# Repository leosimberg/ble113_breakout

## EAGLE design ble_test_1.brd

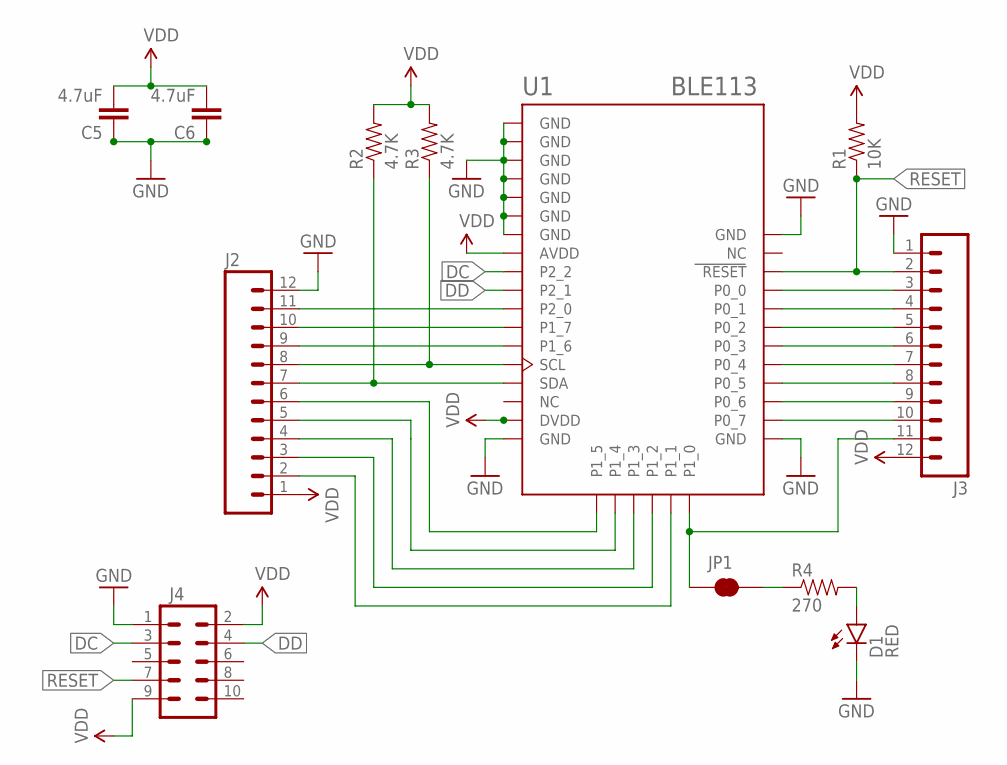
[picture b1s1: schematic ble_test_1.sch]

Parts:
C5, C6: 4.7uF; 0603-CAP
D1: RED; LED-0603
J2, J3: M12PTH; 1X12
J4: M05X2PTH; AVR_ICSP
JP1: JUMPER-PAD-2-NC_BY_TRACE; PAD-JUMPER-2-NC_BY_TRACE_YES_SILK
R1: 10K; 0603-RES
R2, R3: 4.7K; 0603-RES
R4: 270; 0603-RES
U1: BLE113; BLE113-A

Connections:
DC: J4.3, U1.P2_2
DD: J4.4, U1.P2_1
GND: C5.1, C6.1, D1.C, J2.12, J3.1, J4.1, U1.GND, U1.GND@2 (GND), U1.GND@3 (GND), U1.GND@4 (GND), U1.GND@5 (GND), U1.GND@6 (GND), U1.GND@7 (GND), U1.GND@8 (GND), U1.GND@9 (GND), U1.GND@10 (GND)
unnamed: J3.8, U1.P0_5
unnamed: J2.11, U1.P2_0
unnamed: J3.7, U1.P0_4
unnamed: J3.4, U1.P0_1
unnamed: J2.10, U1.P1_7
unnamed: J3.5, U1.P0_2
unnamed: J3.6, U1.P0_3
unnamed: J3.10, U1.P0_7
unnamed: J3.9, U1.P0_6
unnamed: J2.2, U1.P1_1
unnamed: D1.A, R4.2
unnamed: J3.3, U1.P0_0
unnamed: J3.11, JP1.1, U1.P1_0
unnamed: J2.9, U1.P1_6
unnamed: J2.6, U1.P1_5
unnamed: JP1.2, R4.1
unnamed: J2.5, U1.P1_4
unnamed: J2.3, U1.P1_2
unnamed: J2.4, U1.P1_3
RESET: J3.2, J4.7, R1.1, U1.RESET
SCL: J2.7, R2.1, U1.SDA
SDA: J2.8, R3.1, U1.SCL
VDD: C5.2, C6.2, J2.1, J3.12, J4.2, J4.9, R1.2, R2.2, R3.2, U1.AVDD, U1.DVDD

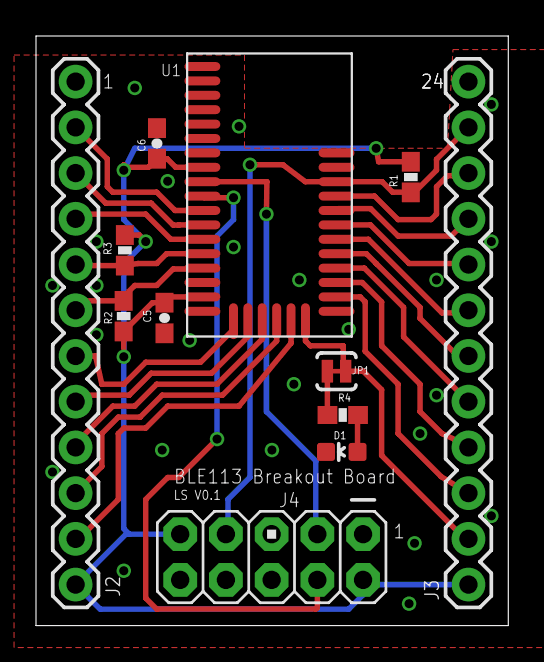
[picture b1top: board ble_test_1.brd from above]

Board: 2 copper layers, 26.2 x 32.8 mm, 12 parts (0 on the bottom side), 26 nets.

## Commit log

2016-10-16 add docs

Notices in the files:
parts and their libraries:
SparkFun-Passives: Licensing: Creative Commons ShareAlike 4.0 International - https://creativecommons.org/licenses/by-sa/4.0
